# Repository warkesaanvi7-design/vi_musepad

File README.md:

# Musepad - Hackpad

Musepad is a four key macropad with a rotary encoder and an OLED display. It runs on KMK firmware and I learned so many new skills, from creating a PCB to coding with CircuitPython and KMK! Musepad is used to control media, specifically music, so the user doesn't have to break their focus to adjust which song is playing or change the volume.

# Features

CAD 3D Printed Case
128x32 OLED Display
EC11 Rotary encoder for volume control
4 Keys

Firmware of Musepad comes with following functions:
 - media control (prev track, pause track, next track)
 - Volume control (volume up and down with scroll knob, mute with a key)
 - Up, Down, Right and Left keys
 - Brightness Control (increase, decrease)

# CAD Model

The model has both the top and bottom parts combined in the assembly. I have also included the switches and encoder part, as well as a cutout for the USB-C plug.

# PCB

This is my PCB, made in KiCad.

Schematic!

PCB!

3D PCB Model!

# Firmware Overview
This hackpad uses KMK firmware for everything.

The rotary encoder changes volume. User can press to pause/play.
The 4 keys currently act as media controllers using the MediaKeys extension in KMK.
The OLED is a a homescreen that says "Saanvi's Musepad". YAY!

# BOM
Here is everything I used to build my Musepad

4x Cherry MX Switches
4x DSA Keycaps
4x M3x5x4 Heatset inserts
4x 1N4148 DO-35 Diodes.
1x 0.91" 128x32 OLED Display
1x EC11 Rotary Encoder
1x XIAO RP2040
1x Case (2 3D printed parts!)

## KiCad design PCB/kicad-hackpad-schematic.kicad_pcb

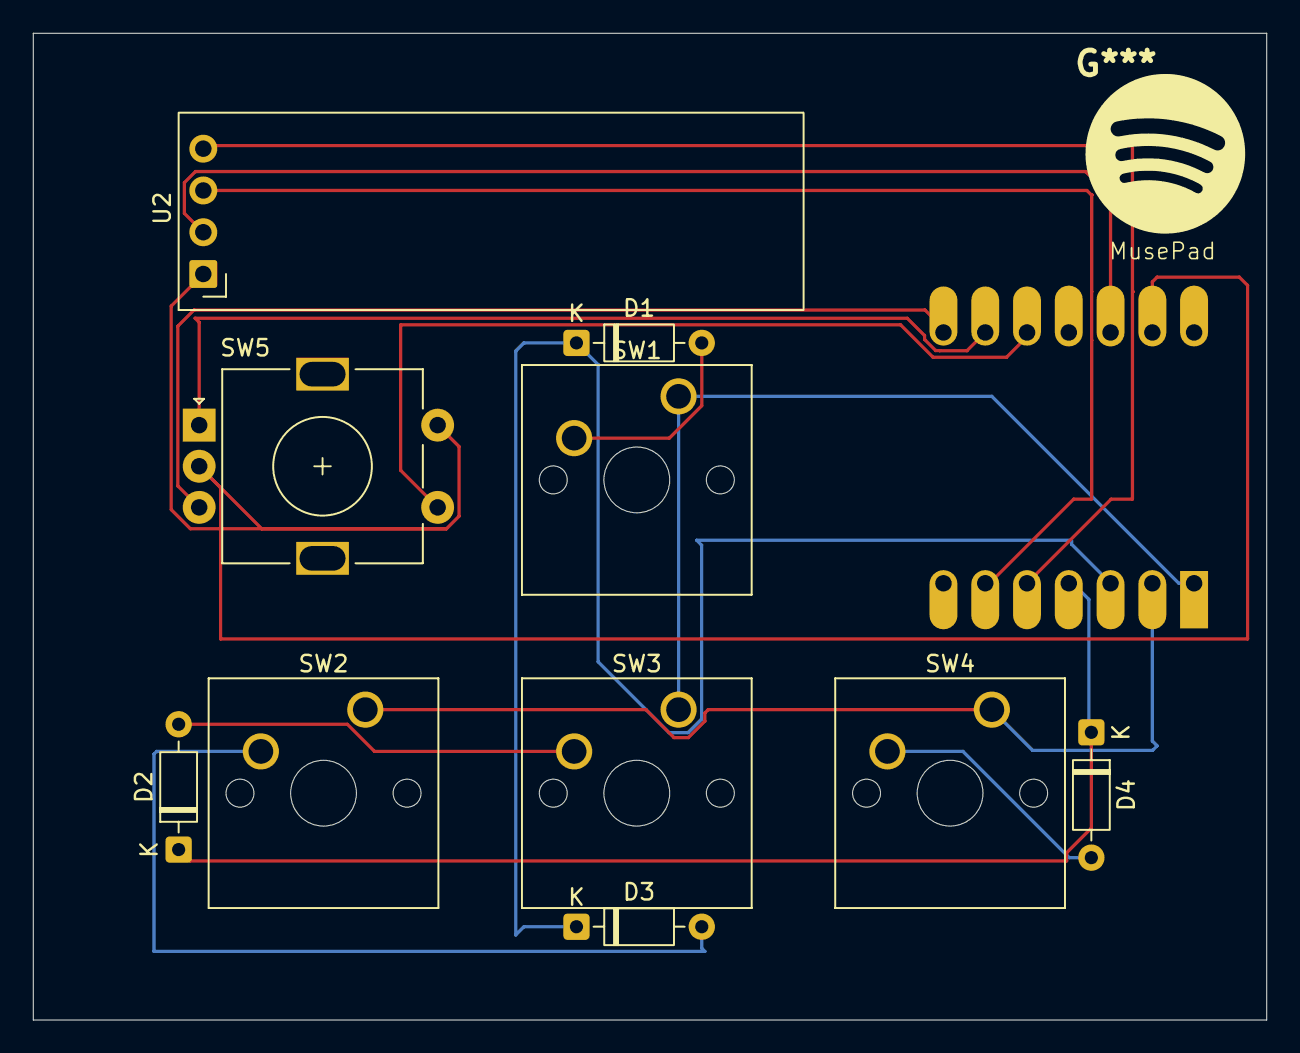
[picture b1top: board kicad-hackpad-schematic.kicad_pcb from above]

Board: 2 copper layers, 75.0 x 60.0 mm, 11 parts (1 on the bottom side), 15 nets.

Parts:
D1, D2, D3, D4: 1N4148; D_DO-35_SOD27_P7.62mm_Horizontal
SW1, SW2, SW3, SW4: SW_Push; SW_Cherry_MX_1.00u_PCB
SW5: RotaryEncoder_Switch; RotaryEncoder_Alps_EC11E-Switch_Vertical_H20mm
U1: MOUDLE-SEEEDUINO-XIAO; XIAO-Generic-Hybrid-14P-2.54-21X17.8MM
U2: ER_OLEDM0.91_1x-I2C

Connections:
3V3: U1.12 (3V3), U2.2 (VCC)
Col1: SW1.1, SW3.1, U1.1 (PA02_A0_D0)
Col2: SW2.1, SW4.1, U1.2 (PA4_A1_D1)
EC11A: SW5.A, U1.9 (PA7_A8_D8_SCK)
EC11B: SW5.B, U1.8 (PB09_A7_D7_RX)
GND: SW5.C, SW5.S2, U1.13 (GND), U2.1 (GND)
unnamed: D1.2 (A), SW1.2
unnamed: D2.2 (A), SW3.2
unnamed: D3.2 (A), SW2.2
unnamed: D4.2 (A), SW4.2
RESw1: SW5.S1, U1.10 (PA5_A9_D9_MISO)
Row1: D1.1 (K), D3.1 (K), U1.3 (PA10_A2_D2)
Row2: D2.1 (K), D4.1 (K), U1.4 (PA11_A3_D3)
SCL: U1.6 (PA9_A5_D5_SCL), U2.3 (SCL)
SDA: U1.5 (PA8_A4_D4_SDA), U2.4 (SDA)
